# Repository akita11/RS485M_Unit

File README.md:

# RS485M Unit

RS485規格の半二重シリアル通信を行うことができるUnitです。
Grove端子でM5Stackシリーズ等のマイコンと接続して使用します。

[M5Stack社のRS485 Unit](https://www.switch-science.com/products/6554)とは異なり、本来のRS485の通信仕様でマルチドロップの1:N通信トポロジを構成できます（詳細は後述）。
データを送信している期間のみ伝送路を送信駆動する制御を行います（通信速度は変更可能）。

伝送路側から最大24Vを供給してマイコン側に5Vを供給することができます。

理論上最大256台まで接続可能な低入力容量型のRS485ドライバを使用しています。

## RS485通信の基本構成と「M5Stack社のRS485 Unit」との相違点

RS485は、2本の伝送路(Line)を使ってシリアルデータ(UART)を送受信する規格です。
規格の詳細と、M5Stack社のRS485 Unitでの留意すべき点は[こちら](https://note.com/akita11/n/n0c082069f98c)を参照してください。

「M5Stack社のRS485 Unit」との相違点は以下です。
（以下のカッコ内の※以下は「M5Stack社のRS485 Unit」の仕様）

- 非送信時には伝送路が非駆動（※"1"で駆動）
- 送信時のみ伝送路を駆動、1バイト単位自動またはGPIOで制御（※常時"1"で駆動）
- 給電入力は48Vまで、24V給電時の過渡応答でも破損しにくい（※給電入力の絶対最大定格が30Vのため24V給電時の過渡応答で破損する場合がある）

## 使い方

基本的には[M5Stack社のRS485 Unit](https://www.switch-science.com/products/6554)と同じ使い方ですが、送信制御のみ異なり、以下の通りの仕様です。

なおJP5をショートすると伝送路の終端抵抗（120Ω）をONにできます。
またJP6とJP7をショートすると、伝送路のプルアップ・プルダウンを有効にできます（Aプルアップ、Bがプルダウン（5.1kΩ））。

### データ送信

データ送信時には、送信している期間のみDriverが自動的に有効となり、伝送路Lineを駆動します。

スタートビット検出から1バイト分（10bit分=STARTビット+データ8ビット+STOPビット）の時間だけ自動的にDriverが有効となり、伝送路にデータを送信します（伝送路を駆動中はLEDが点灯）。
通信方式はN81（8ビット・STOPビット1ビット、パリティなし）で固定です。
初期設定では通信速度は9600bpsです。

データ送信時にDriverを有効とする時間は、データ転送速度（ボーレート）に依存するため、後述の方法で変更できます

データ送信中は、Receiverは無効となり、データを受信しません。
JP8を2-3側に切り替えると、伝送路レシーバReceiverを常時有効に設定できますが、この場合は、自分のDriverが送信したデータを常時受信することになります。

### ピン配置

- p1: RXD（マイコン側の受信。本ユニットはRS485受信データの出力）
- p2: TXD（マイコン側の送信。本ユニットはRS485送信データの入力）
- p3: +5V
- p4: GND

### 伝送速度（ボーレート）の変更

Grove側からBREAK信号（一定時間以上、データ線を"L"に保持）することで、伝送速度変更モードに入り、LEDが点滅します。
この状態で、設定したい伝送速度（ボーレート）で以下のいずれか1バイトを送信することで、その波形から伝送速度を検出し、伝送速度の設定（Driverを有効とする時間）を変更します。
設定された伝送速度は電源を切っても保存されます。

- 'U' (0x55) : 1バイト伝送モード。1バイト伝送終了後の伝送路ドライバがDisableに戻ります。（LEDが3回点滅）
- '5' (0x35) : 連続伝送モード。送信開始語、一定時間データが送られなかった場合に伝送路ドライバがDisableに戻ります。（LEDが5回点滅）

なおBREAK信号は、PC用ターミナルソフトでも送出ができます（例えばTeraTermではAlt+B、MacのscreenコマンドではCtrl+A→Ctr+B）。
[Groveケーブル-USBシリアル接続ケーブル](https://www.switch-science.com/products/9460)などを使って、PCと接続して設定変更や送受信テストができます。

### 電源給電の設定

デフォルトでは、RS485ドライバは5V給電（外部12/24Vから生成した5V）ですが、以下のように変更できます。
なおGrove端子側から5Vを供給することもできます。

- JP9: 給電方法
  - 1-2間: 外部12/24Vから5Vを生成、本体とGroveへ供給（デフォルト）
  - 2-3間: 外部給電をそのまま本体・Groveへ接続（※この場合は外部からの給電電圧は5Vとしてください。5V以上の電圧を加えると破損する場合があります）

## Author

Junichi Akita (@akita11) / akita@ifdl.jp

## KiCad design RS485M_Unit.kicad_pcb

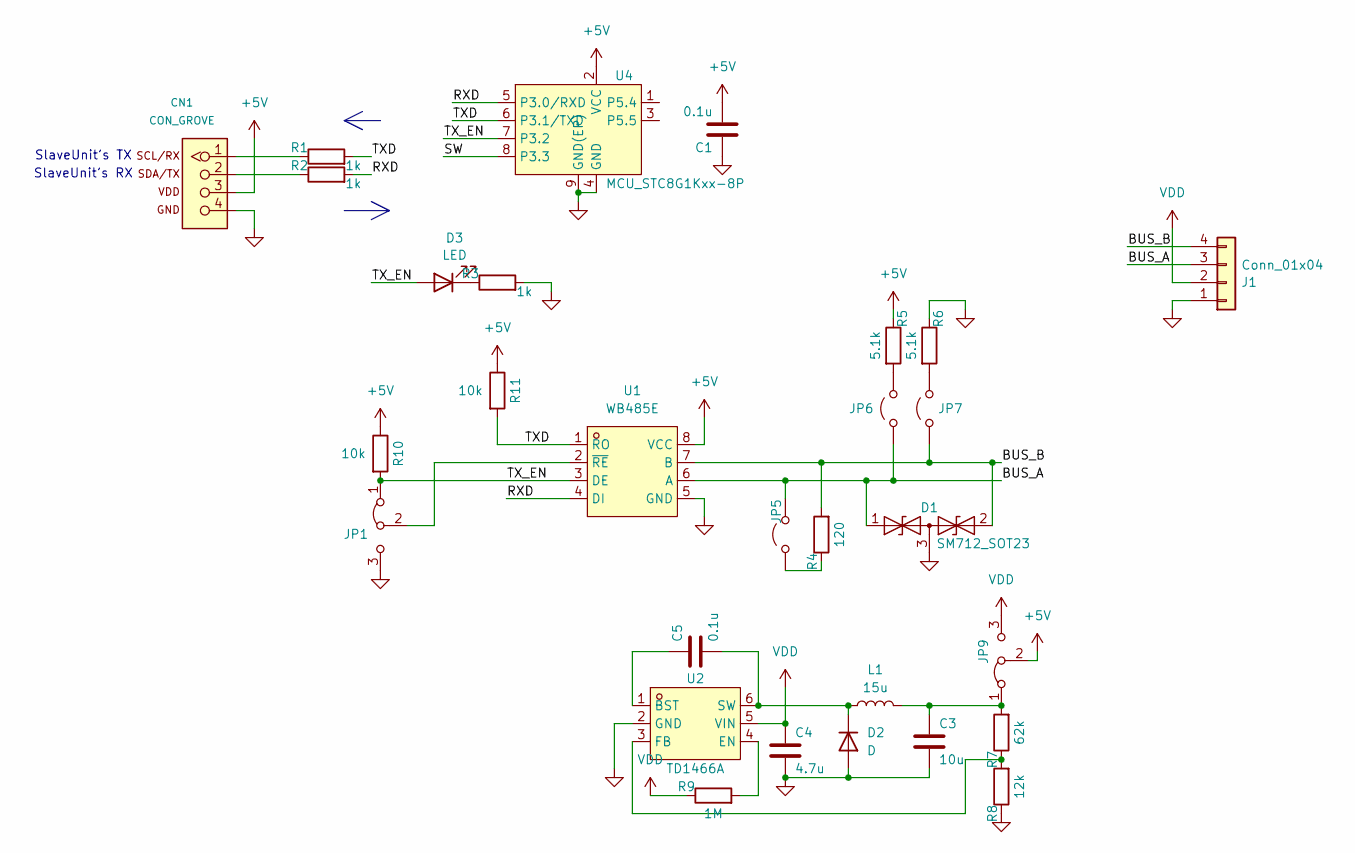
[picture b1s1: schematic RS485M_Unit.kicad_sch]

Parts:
C1, C5: 0.1u; C_0603_1608Metric; LCSC C14663
C3: 10u; C_0603_1608Metric; LCSC C19702
C4: 4.7u; C_0603_1608Metric; LCSC C167655
CN1: CON_GROVE; CON_GROVE_H
D1: SM712_SOT23; SOT-23; LCSC C5180237
D2: D; D_SOD-323F
D3: LED; LED_0603_1608Metric; LCSC C2286
J1: Conn_01x04; CON_HT396R_4P_hole0.8sq
JP1: Jumper_3_Bridged12; SolderJumper-3_P1.3mm_Bridged12_Pad1.0x1.5mm
JP5, JP6, JP7: Jumper_2_Open; SolderJumper-2_P1.3mm_Open_Pad1.0x1.5mm
JP9: Jumper_3_Bridged12; SolderJumper-3_P1.3mm_Bridged2Bar12_Pad1.0x1.5mm
L1: 15u; L_CD43; LCSC C5289403
R1, R2, R3: 1k; R_0603_1608Metric; LCSC C21190
R4: 120; R_0603_1608Metric; LCSC C286567
R5, R6: 5.1k; R_0603_1608Metric; LCSC C23186
R7: 62k; R_0603_1608Metric; LCSC C3017756
R8: 12k; R_0603_1608Metric; LCSC C3017713
R9: 1M; R_0603_1608Metric; LCSC C2907115
R10, R11: 10k; R_0603_1608Metric; LCSC C25804
U1: WB485E; SOIC-8_L5.0-W4.0-P1.27-LS6.0-BL; LCSC Part C42460582
U2: TD1466A; SOT-23-6_L2.9-W1.7-P0.95-LS2.8-BL; LCSC Part C51928156
U4: MCU_STC8G1Kxx-8P; DFN-8-1EP_3x3mm_P0.5mm_EP1.65x2.38mm; LCSC C915664

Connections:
+5V: C1.2, CN1.3, JP9.2 (C), R5.1, R10.1, R11.1, U1.8 (VCC), U4.2 (VCC)
/BUS_A: D1.1 (A1), J1.3, JP5.2 (B), JP6.1 (A), U1.6 (A)
/BUS_B: D1.2 (A2), J1.4, JP7.1 (A), R4.2, U1.7 (B)
/RXD: R2.2, U1.4 (DI), U4.5 (P3.0/RXD)
/SW: U4.8 (P3.3)
/TXD: R1.2, R11.2, U1.1 (RO), U4.6 (P3.1/TXD)
/TX_EN: D3.2 (A), JP1.1 (A), R10.2, U1.3 (DE), U4.7 (P3.2)
GND: C1.1, C3.2, C4.2, CN1.4, D1.3 (common), D2.2 (A), J1.1, JP1.3 (B), R3.2, R6.1, R8.1, U1.5 (GND), U2.2 (GND), U4.4 (GND), U4.9 (GND(EP))
unnamed: CN1.1, R1.1
unnamed: CN1.2, R2.1
unnamed: C5.2, D2.1 (K), L1.1, U2.6 (SW)
unnamed: D3.1 (K), R3.1
unnamed: JP1.2 (C), U1.2 (~RE)
unnamed: JP5.1 (A), R4.1
unnamed: JP6.2 (B), R5.2
unnamed: JP7.2 (B), R6.2
unnamed: C3.1, JP9.1 (A), L1.2, R7.2
unnamed: C5.1, U2.1 (BST)
unnamed: R9.2, U2.4 (EN)
unnamed: R7.1, R8.2, U2.3 (FB)
VDD: C4.1, J1.2, JP9.3 (B), R9.1, U2.5 (VIN)

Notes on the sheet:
SlaveUnit's TX
SlaveUnit's RX

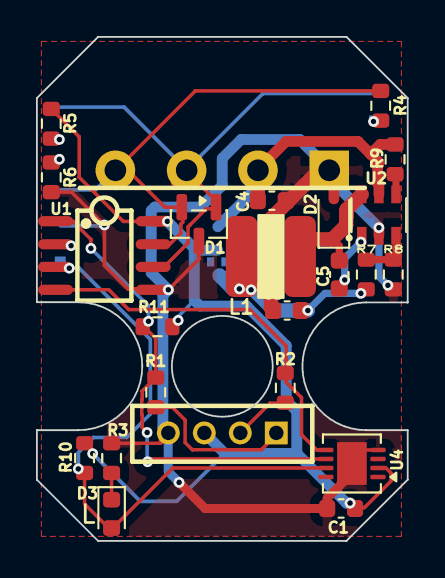
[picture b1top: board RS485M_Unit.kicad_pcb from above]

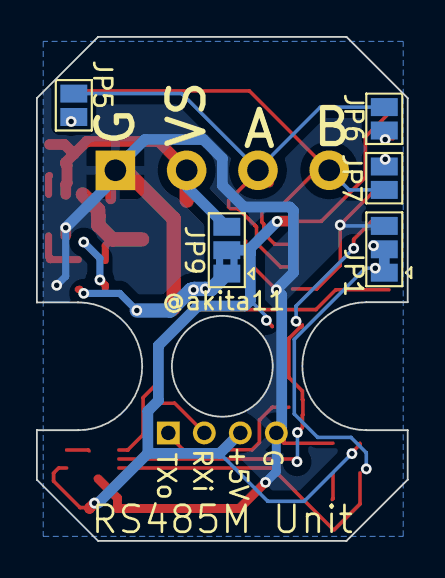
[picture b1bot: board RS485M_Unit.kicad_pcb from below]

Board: 2 copper layers, 20.6 x 28.0 mm, 29 parts (5 on the bottom side), 20 nets.

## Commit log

2026-03-20 update FW
2026-04-01 add pin assign
2026-04-01 add photo, JP6/7 modify
2026-04-01 fix photo file name
